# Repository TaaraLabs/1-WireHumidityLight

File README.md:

1-WireHumidityLight
===================

1-Wire Temperature, Humidity and Light sensor

[WebSite](https://taaralabs.eu/ol1)

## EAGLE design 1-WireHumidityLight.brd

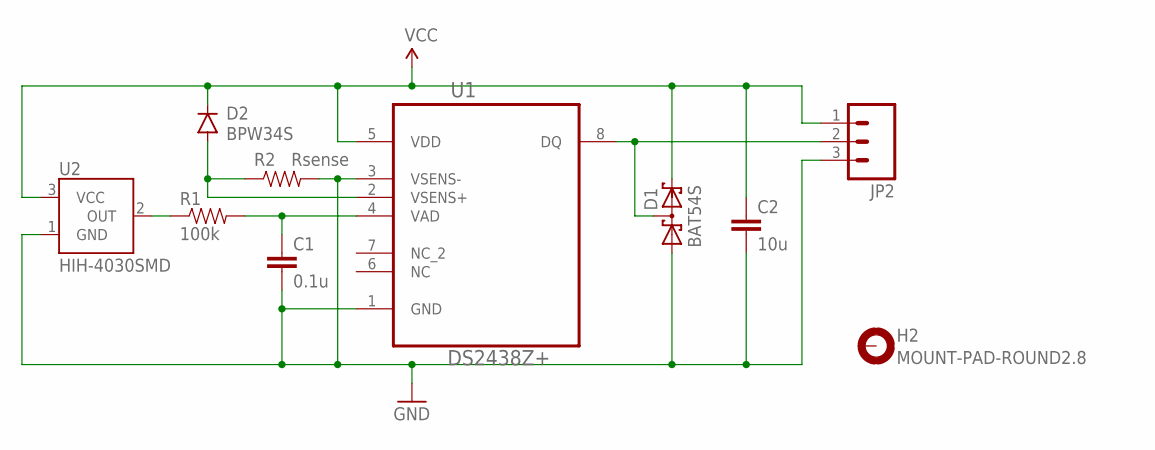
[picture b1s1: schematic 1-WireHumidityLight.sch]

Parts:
C1: 0.1u; 0603-CAP
C2: 10u; 0603-CAP
D1: BAT54S; SOT23
D2: BPW34S
H2: MOUNT-PAD-ROUND2.8; 2,8-PAD
JP2: M03LONGPADS; 1X03_LONGPADS
R1: 100k; 0603-RES
R2: Rsense; 0603-RES
U1: DS2438Z+; SOIC127P600X175-8N
U2: HIH-4030SMD; HIH-4030

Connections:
GND: C1.2, C2.2, D1.1 (A1), JP2.3, R2.2, U1.1 (GND), U1.3 (VSENS-), U2.1 (GND)
unnamed: R1.1, U2.2 (OUT)
unnamed: D2.P$1 (A), R2.1, U1.2 (VSENS+)
QD: D1.3 (C1A2), JP2.2, U1.8 (DQ)
VAD: C1.1, R1.2, U1.4 (VAD)
VCC: C2.1, D1.2 (C2), D2.P$2 (C), JP2.1, U1.5 (VDD), U2.3 (VCC)

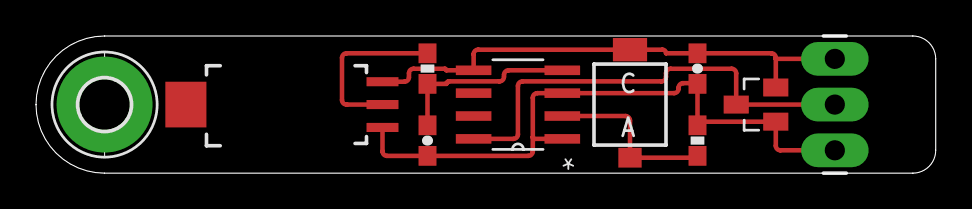
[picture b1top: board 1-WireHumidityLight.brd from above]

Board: 2 copper layers, 50.0 x 7.6 mm, 11 parts (1 on the bottom side), 6 nets.

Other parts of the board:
U$3: OSHW-LOGO-S

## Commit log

2016-11-20 Added correct project name and URL
2017-04-11 product pictures

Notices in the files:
parts and their libraries:
SparkFun-Sensors: Licensing: CC v3.0 Share-Alike You are welcome to use this library for commercial purposes.
